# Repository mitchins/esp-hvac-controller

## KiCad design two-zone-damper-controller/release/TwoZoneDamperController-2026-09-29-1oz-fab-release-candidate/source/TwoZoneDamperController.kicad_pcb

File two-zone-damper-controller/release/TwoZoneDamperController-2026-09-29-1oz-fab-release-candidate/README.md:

# Two-Zone Damper Controller - 1 oz fabrication release candidate

This is the complete 2026-09-29 release candidate for the accepted routed board, revised from the earlier 2 oz release solely to record and manufacture the validated **1 oz finished outer copper** stackup. The schematic, footprints, placement, board outline, and routing geometry are otherwise unchanged.

## Contents

- `fabrication/` - upload-ready Gerber/drill ZIP plus individual source files.
- `source/` - KiCad project, PCB, schematic, symbols, constraints, and local footprints.
- `documentation/` - build, wiring, commissioning, use-case, and fabrication guidance.
- `firmware/` - separate ESPHome HVAC and generic 12 V profiles.
- `physical-fit/` - routed 1:1 physical-fit sheet; print at 100% / Actual Size.
- `validation/` - current ERC and PCB-DRC status.

## Mandatory fabrication/order contract

- Two-layer FR-4, 1.60 mm nominal board thickness.
- **1 oz (35 um) finished copper on F.Cu and B.Cu.** Confirm this standard option in the JLCPCB order form. Do not select the 2 oz surcharge for this release.
- No assembly or stencil is assumed.
- Field side is isolated only: **never connect mains**.

## Field-side limits

- Install only one field-supply/use mode: 24 VAC HVAC or 12 V SELV generic loads.
- 10 A maximum total field current and 6 A maximum per generic resistive output.
- Select F1 for the measured load/inrush, application-specific AC/DC interrupt rating, and connected wiring. Never install a fuse above 10 A.
- Do not alter the accepted paired 5 mm positive paths, 4 mm output branches, or B.Cu field-return pour when using 1 oz copper.

Release hold: complete the final actual-component overlay using the supplied fit sheet before fabrication upload.

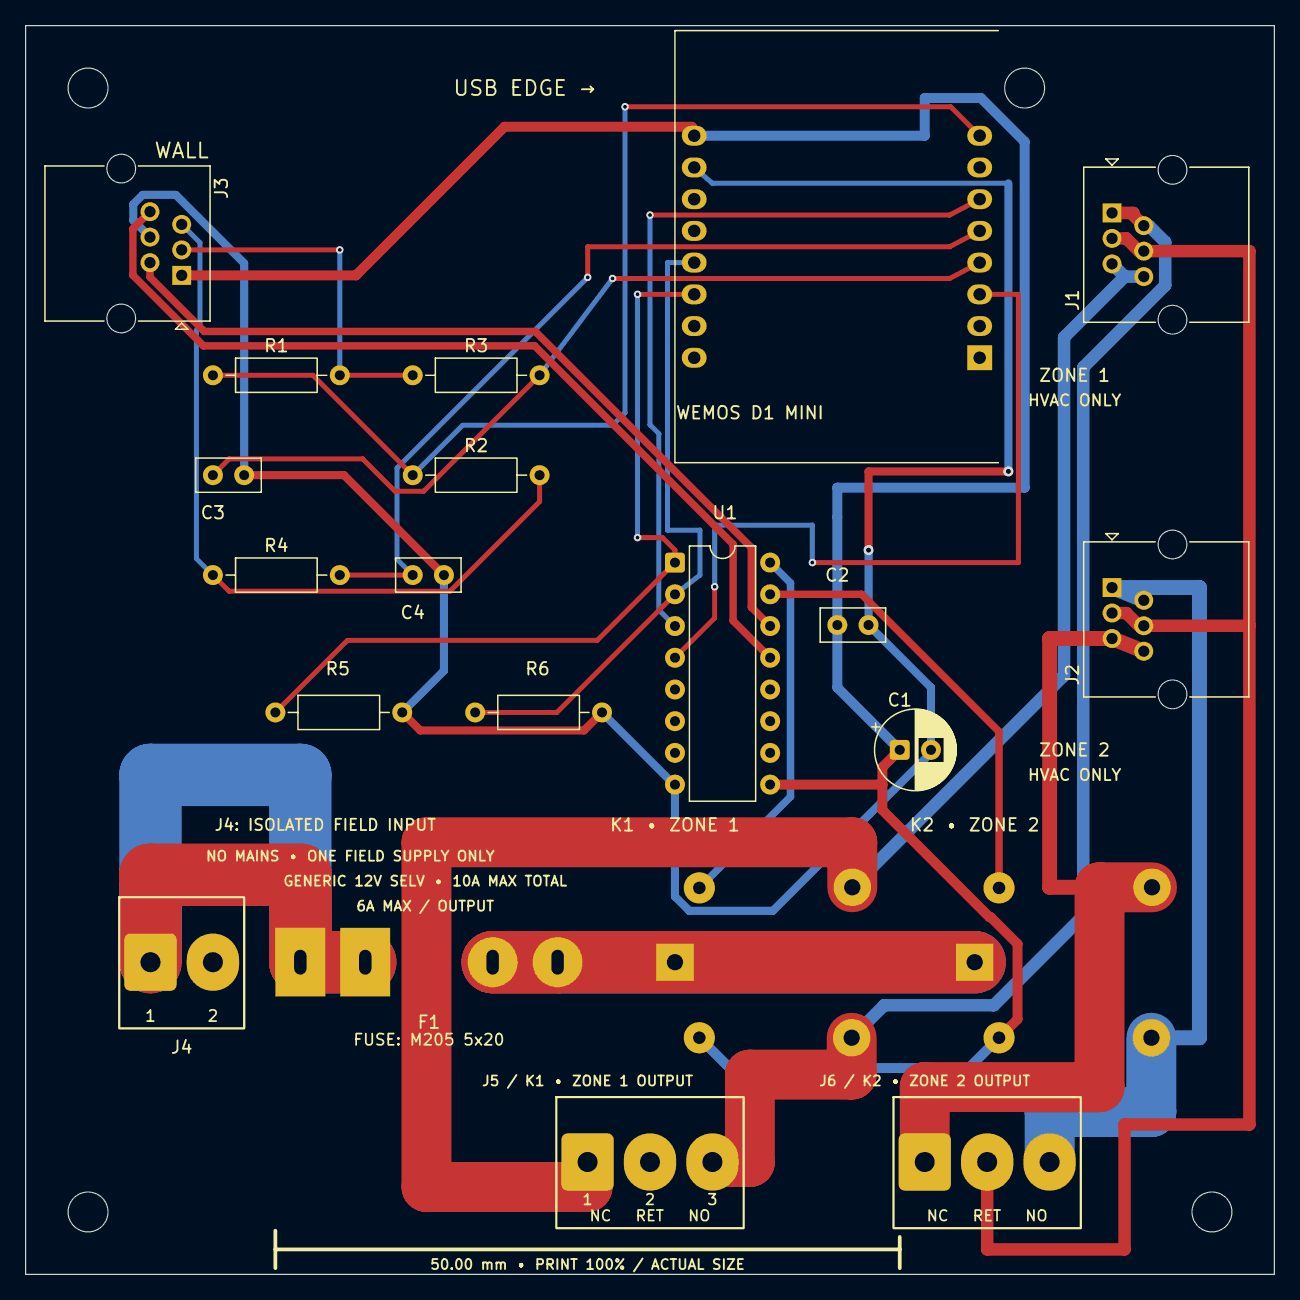
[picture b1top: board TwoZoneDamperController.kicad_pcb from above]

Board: 2 copper layers, 100.0 x 100.0 mm, 25 parts (0 on the bottom side), 22 nets.

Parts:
C1: 100uF 10V; CP_Radial_D6.3mm_P2.50mm
C2: 100nF; C_Disc_D5.0mm_W2.5mm_P2.50mm
C3, C4: 100nF SW filter; C_Disc_D5.0mm_W2.5mm_P2.50mm
F1: 2x ALTRONICS S5983 M205 CLIPS — FUSE TBD; Altronics_S5983_M205_2Clip_P20.60mm
J1: ZONE 1 DAMPER RJ12 - HVAC 24VAC ONLY; RJ25_Wayconn_MJEA-660X1_Horizontal
J2: ZONE 2 DAMPER RJ12 - HVAC 24VAC ONLY; RJ25_Wayconn_MJEA-660X1_Horizontal
J3: WALL CONTROL RJ12; RJ25_Wayconn_MJEA-660X1_Horizontal
J4: ZPWAN 126-5.0-02P - FIELD SUPPLY INPUT; ZPWAN_126_5_0_02P
J5: KF128-5.0/5.08-3P - ZONE 1 OUTPUT; ZPWAN_126_5_0_J5_Left
J6: KF128-5.0/5.08-3P - ZONE 2 OUTPUT; ZPWAN_126_5_0_J6_Right
K1, K2: SRD-05VDC-SL-C 5V; Songle_SRD_05VDC_SL_C
MH1, MH2, MH3, MH4: MountingHole_3.2mm
R1: 2k2 SW_A pull-up; R_Axial_DIN0207_L6.3mm_D2.5mm_P10.16mm_Horizontal
R2: 2k2 SW_B pull-up; R_Axial_DIN0207_L6.3mm_D2.5mm_P10.16mm_Horizontal
R3: 1k SW_A series; R_Axial_DIN0207_L6.3mm_D2.5mm_P10.16mm_Horizontal
R4: 1k SW_B series; R_Axial_DIN0207_L6.3mm_D2.5mm_P10.16mm_Horizontal
R5: 10k RELAY1 pulldown; R_Axial_DIN0207_L6.3mm_D2.5mm_P10.16mm_Horizontal
R6: 10k RELAY2 pulldown; R_Axial_DIN0207_L6.3mm_D2.5mm_P10.16mm_Horizontal
U1: ULN2003A; DIP-16_W7.62mm
U2: Wemos D1 Mini (removable); Wemos_D1_mini_FemaleSocket_DONOR

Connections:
+3V3: R1.1, R2.1, U2.8
+5V_USB: C1.1, C2.1, J3.1, K1.2, K2.2, U1.9, U2.9
FIELD_SUPPLY_POS_FUSED: F1.2, K1.3, K2.3
FIELD_SUPPLY_POS_IN: F1.1, J4.1
FIELD_SUPPLY_RETURN: J1.3, J1.4, J2.3, J2.4, J4.2, J5.2, J6.2
GND: C1.2, C2.2, C3.2, C4.2, J3.4, R5.2, R6.2, U1.8, U2.10
K1_COIL_LOW: K1.5, U1.16
K2_COIL_LOW: K2.5, U1.15
LIVING_BUTTON: C3.1, R3.2, U2.4
LIVING_BUTTON_RAW: J3.3, R1.2, R3.1
LIVING_LED_DRIVE: U1.3, U2.6
LIVING_LED_RETURN: J3.2, U1.14
RELAY1_IN: R5.1, U1.1, U2.14
RELAY2_IN: R6.1, U1.2, U2.13
ROOMS_BUTTON: C4.1, R4.2, U2.5
ROOMS_BUTTON_RAW: J3.5, R2.2, R4.1
ROOMS_LED_DRIVE: U1.4, U2.3
ROOMS_LED_RETURN: J3.6, U1.13
Z1_CLOSE: J1.1, J1.2, J5.3, K1.1
Z1_OPEN: J1.5, J1.6, J5.1, K1.6
Z2_CLOSE: J2.1, J2.2, J6.3, K2.1
Z2_OPEN: J2.5, J2.6, J6.1, K2.6

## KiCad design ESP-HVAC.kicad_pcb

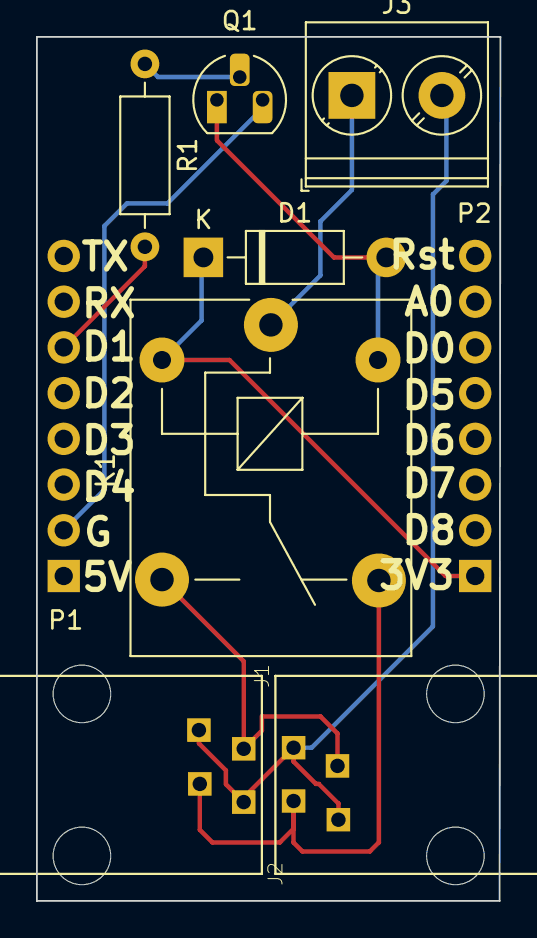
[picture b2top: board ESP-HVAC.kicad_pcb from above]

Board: 2 copper layers, 25.8 x 48.0 mm, 9 parts (0 on the bottom side), 9 nets.

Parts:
D1: 1N4007; D_DO-41_SOD81_P10.16mm_Horizontal
J1, J2: 4P4C; RJ11-4P
J3: Screw_Terminal_01x02; TerminalBlock_Phoenix_PT-1,5-2-5.0-H_1x02_P5.00mm_Horizontal
K1: SRD-03VDC-SL-C; Relay_SPDT_SANYOU_SRD_Series_Form_C
P1, P2: CONN_01X08; D1_mini_Pin_Header
Q1: BC547; TO-92_HandSolder
R1: R_Small; R_Axial_DIN0207_L6.3mm_D2.5mm_P10.16mm_Horizontal

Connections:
/+3.3V: D1.1, K1.2, P2.1
/D1: P1.6, R1.2
/GND: P1.2, Q1.3
unnamed: D1.2, K1.5, Q1.1
unnamed: J1.1, J2.4, K1.3
unnamed: J1.2, J1.3, J2.2, J2.3, J3.2
unnamed: J1.4, J2.1, K1.4
unnamed: J3.1, K1.1
unnamed: Q1.2, R1.1

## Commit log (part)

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2021-01-25 Add gitignore
2021-01-25 initial sketch
2021-01-26 Revisions to to-92, relay
2021-01-27 update footprint
2021-01-29 Simple 50x50 board with inverse zone control off one relay
2021-01-30 esp-01 variant
2021-01-30 rough initial d1 mini shield concept
2021-03-20 some progress
2021-03-20 add cache lib
